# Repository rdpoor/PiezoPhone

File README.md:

# PiezoPhone
Arduino-based Digital Marimba / Xylophone / Glockenspiel

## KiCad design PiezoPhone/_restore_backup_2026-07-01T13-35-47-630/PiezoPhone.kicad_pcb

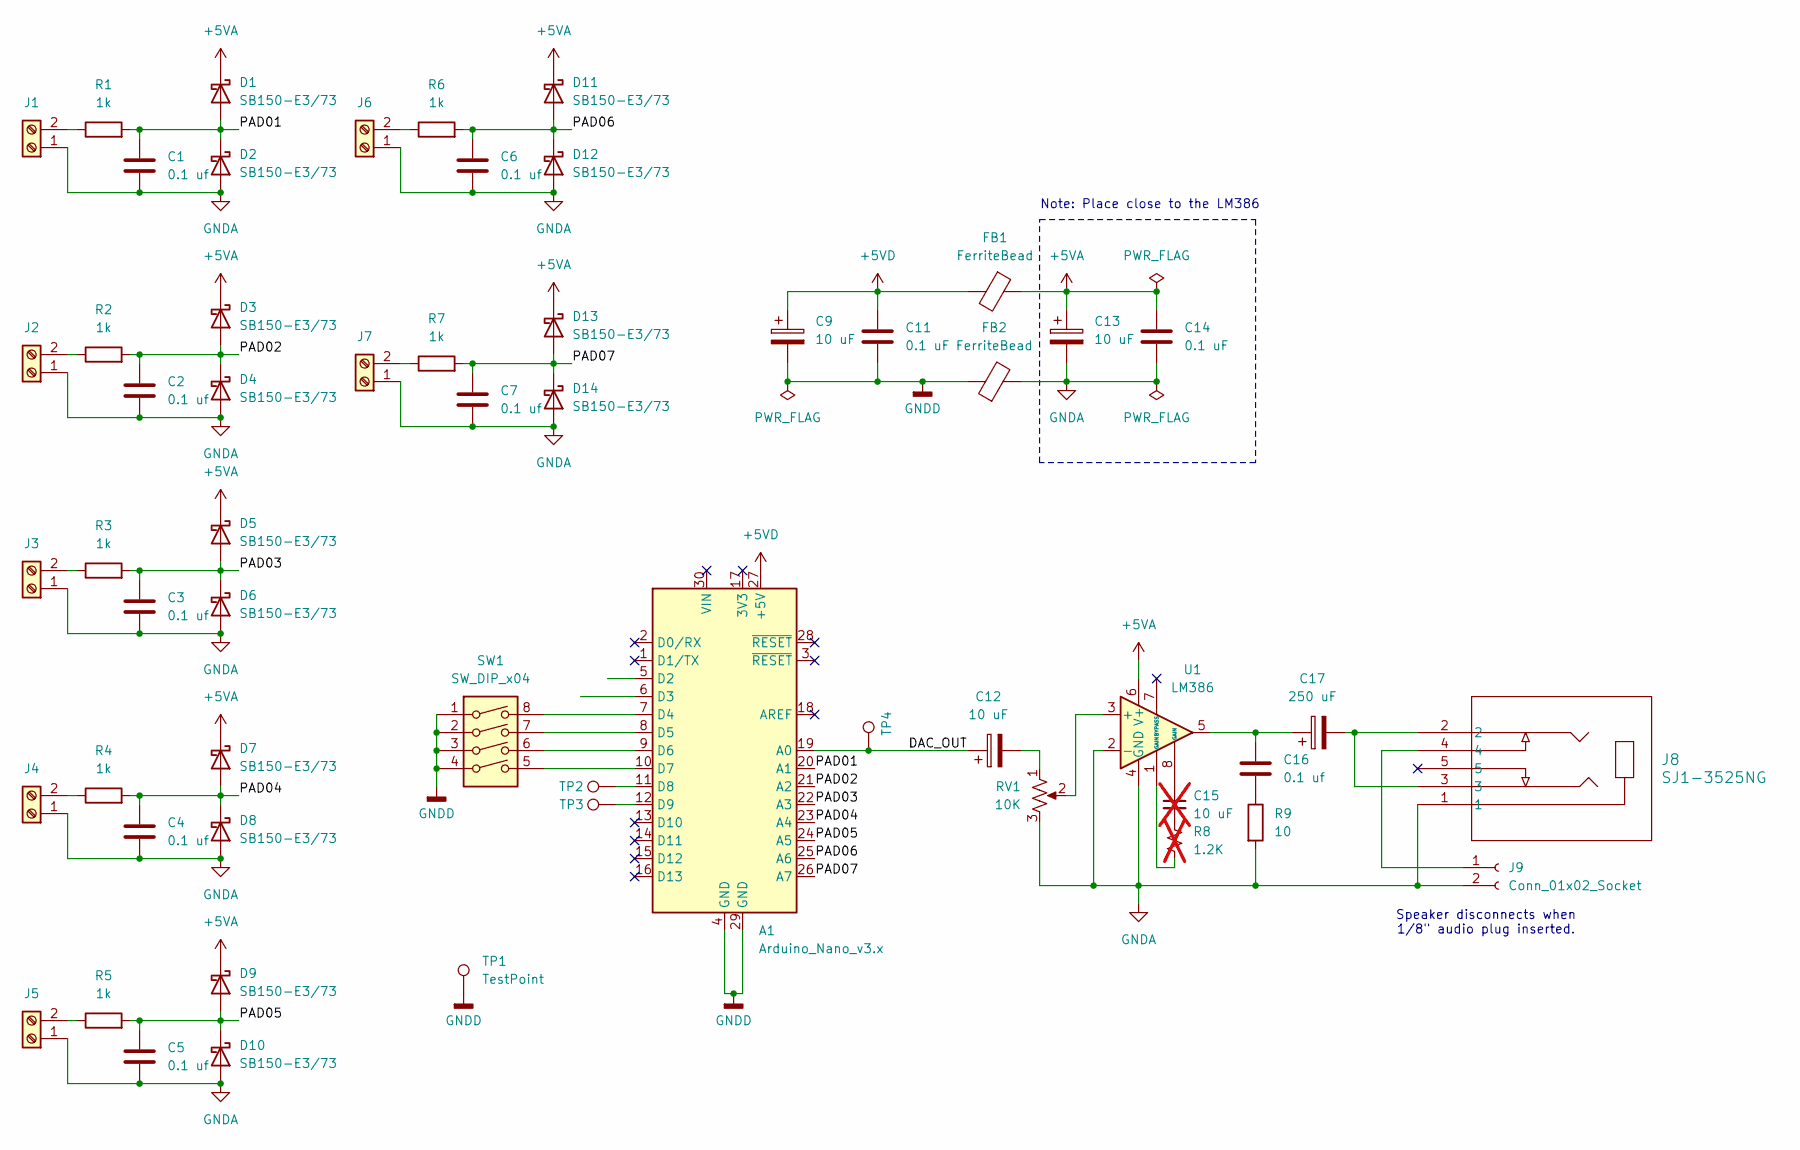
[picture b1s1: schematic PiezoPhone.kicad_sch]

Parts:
A1: Arduino_Nano_v3.x; Arduino_Nano
C1, C2, C3, C4, C5, C6, C7, C16: 0.1 uf; C_Disc_D4.7mm_W2.5mm_P5.00mm
C9, C12, C13: 10 uF; CP_Radial_D5.0mm_P2.50mm
C11, C14: 0.1 uF; C_Disc_D4.7mm_W2.5mm_P5.00mm
C15: 10 uF; CP_Radial_D5.0mm_P2.50mm; not fitted
C17: 250 uF; CP_Radial_D8.0mm_P3.50mm
D1, D2, D3, D4, D5, D6, D7, D8, D9, D10, D11, D12, D13, D14: SB150-E3/73; D_DO-41_SOD81_P10.16mm_Horizontal
FB1, FB2: FerriteBead; R_Axial_DIN0411_L9.9mm_D3.6mm_P12.70mm_Horizontal
J1, J2, J3, J4, J5, J6, J7: Screw_Terminal_01x02; PhoenixContact_MSTBVA_2,5_2-G_1x02_P5.00mm_Vertical
J8: SJ1-3525NG; SJ1-3525NG_CUD
J9: Conn_01x02_Socket; JST_PH_S2B-PH-K_1x02_P2.00mm_Horizontal
R1, R2, R3, R4, R5, R6, R7: 1k; R_Axial_DIN0207_L6.3mm_D2.5mm_P15.24mm_Horizontal
R8: 1.2K; R_Axial_DIN0207_L6.3mm_D2.5mm_P15.24mm_Horizontal; not fitted
R9: 10; R_Axial_DIN0207_L6.3mm_D2.5mm_P15.24mm_Horizontal
RV1: 10K; TRIM_3352T-1-103LF
SW1: SW_DIP_x04; DIP-8_W7.62mm_Socket
TP1, TP2, TP3, TP4: TestPoint; TestPoint_Keystone_5005-5009_Compact
U1: LM386; DIP-8_W7.62mm_Socket_LongPads

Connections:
+5VA: C13.1, C14.1, D1.1 (K), D3.1 (K), D5.1 (K), D7.1 (K), D9.1 (K), D11.1 (K), D13.1 (K), FB1.1, U1.6 (V+)
+5VD: A1.27 (+5V), C9.1, C11.1, FB1.2
/DAC_OUT: A1.19 (A0), C12.1, TP4.1 (1_1)
/PAD01: A1.20 (A1), C1.1, D1.2 (A), D2.1 (K), R1.2
/PAD02: A1.21 (A2), C2.1, D3.2 (A), D4.1 (K), R2.2
/PAD03: A1.22 (A3), C3.1, D5.2 (A), D6.1 (K), R3.2
/PAD04: A1.23 (A4), C4.1, D7.2 (A), D8.1 (K), R4.2
/PAD05: A1.24 (A5), C5.1, D9.2 (A), D10.1 (K), R5.2
/PAD06: A1.25 (A6), C6.1, D11.2 (A), D12.1 (K), R6.2
/PAD07: A1.26 (A7), C7.1, D13.2 (A), D14.1 (K), R7.2
GNDA: C1.2, C2.2, C3.2, C4.2, C5.2, C6.2, C7.2, C13.2, C14.2, D2.2 (A), D4.2 (A), D6.2 (A), D8.2 (A), D10.2 (A), D12.2 (A), D14.2 (A), FB2.2, J1.1, J2.1, J3.1, J4.1, J5.1, J6.1, J7.1, J8.1, J9.2, R9.2, RV1.3, U1.2 (-), U1.4 (GND)
GNDD: A1.4 (GND), A1.29 (GND), C9.2, C11.2, FB2.1, SW1.1, SW1.2, SW1.3, SW1.4, TP1.1 (1_1)
unnamed: A1.7 (D4), SW1.8
unnamed: A1.8 (D5), SW1.7
unnamed: A1.9 (D6), SW1.6
unnamed: A1.10 (D7), SW1.5
unnamed: A1.11 (D8), TP2.1 (1_1)
unnamed: A1.12 (D9), TP3.1 (1_1)
unnamed: C12.2, RV1.1
unnamed: C15.1, U1.8 (GAIN)
unnamed: C15.2, R8.1
unnamed: C16.1, C17.1, U1.5
unnamed: C16.2, R9.1
unnamed: C17.2, J8.2, J8.3
unnamed: J1.2, R1.1
unnamed: J2.2, R2.1
unnamed: J3.2, R3.1
unnamed: J4.2, R4.1
unnamed: J5.2, R5.1
unnamed: J6.2, R6.1
unnamed: J7.2, R7.1
unnamed: J8.4, J9.1
unnamed: R8.2, U1.1 (GAIN)
unnamed: RV1.2, U1.3 (+)

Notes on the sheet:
Speaker disconnects when 1/8" audio plug inserted.
Note: Place close to the LM386

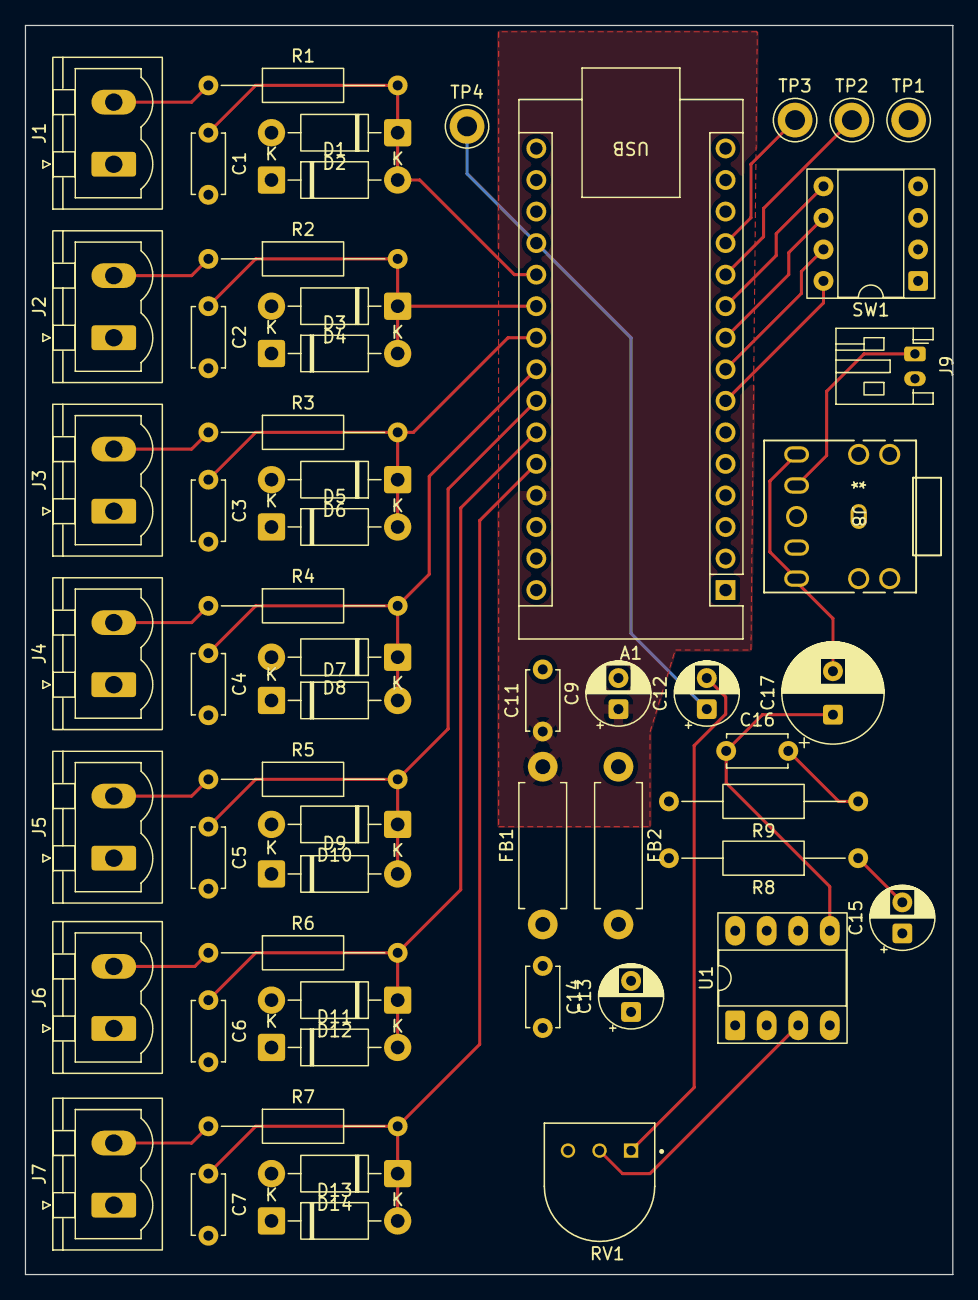
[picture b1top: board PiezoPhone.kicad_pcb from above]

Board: 2 copper layers, 74.7 x 100.6 mm, 57 parts (0 on the bottom side), 34 nets.

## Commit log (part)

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2026-05-29 Initial schematic and footprints
2026-06-02 Preparing to travel
2026-06-12 adding footprints
